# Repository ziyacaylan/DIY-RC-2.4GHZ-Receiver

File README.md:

# DIY-RC-2.4GHZ-Receiver
https://www.thingiverse.com/zii/designs
DIY-RC-2.4GHZ-Receiver

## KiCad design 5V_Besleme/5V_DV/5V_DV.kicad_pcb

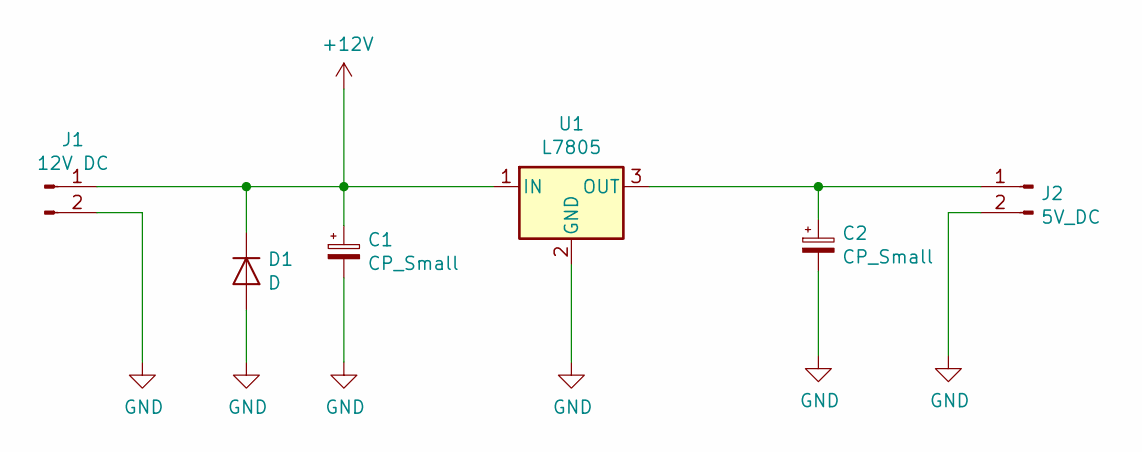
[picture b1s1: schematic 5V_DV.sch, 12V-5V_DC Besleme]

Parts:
C1, C2: CP_Small; CP_Elec_8x6.7
D1: D; D_2114
J1: 12V DC; Socket_Strip_Straight_2x01_Pitch2.54mm
J2: 5V_DC; Socket_Strip_Straight_2x01_Pitch2.54mm
U1: L7805; TO-252-2

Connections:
+12V: C1.1, D1.1 (K), J1.1, U1.1 (IN)
GND: C1.2, C2.2, D1.2 (A), J1.2, J2.2, U1.2 (GND)
unnamed: C2.1, J2.1, U1.3 (OUT)

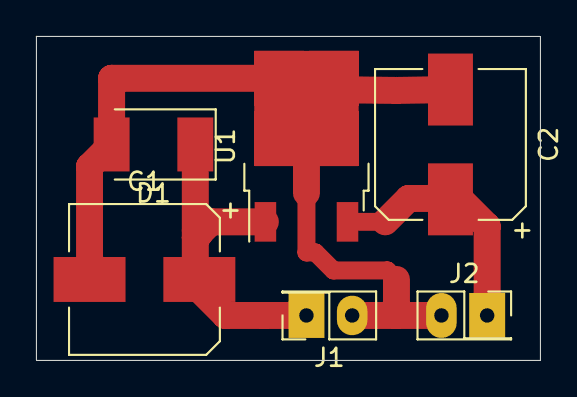
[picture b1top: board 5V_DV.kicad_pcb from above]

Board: 2 copper layers, 28.0 x 18.0 mm, 6 parts (0 on the bottom side), 3 nets.

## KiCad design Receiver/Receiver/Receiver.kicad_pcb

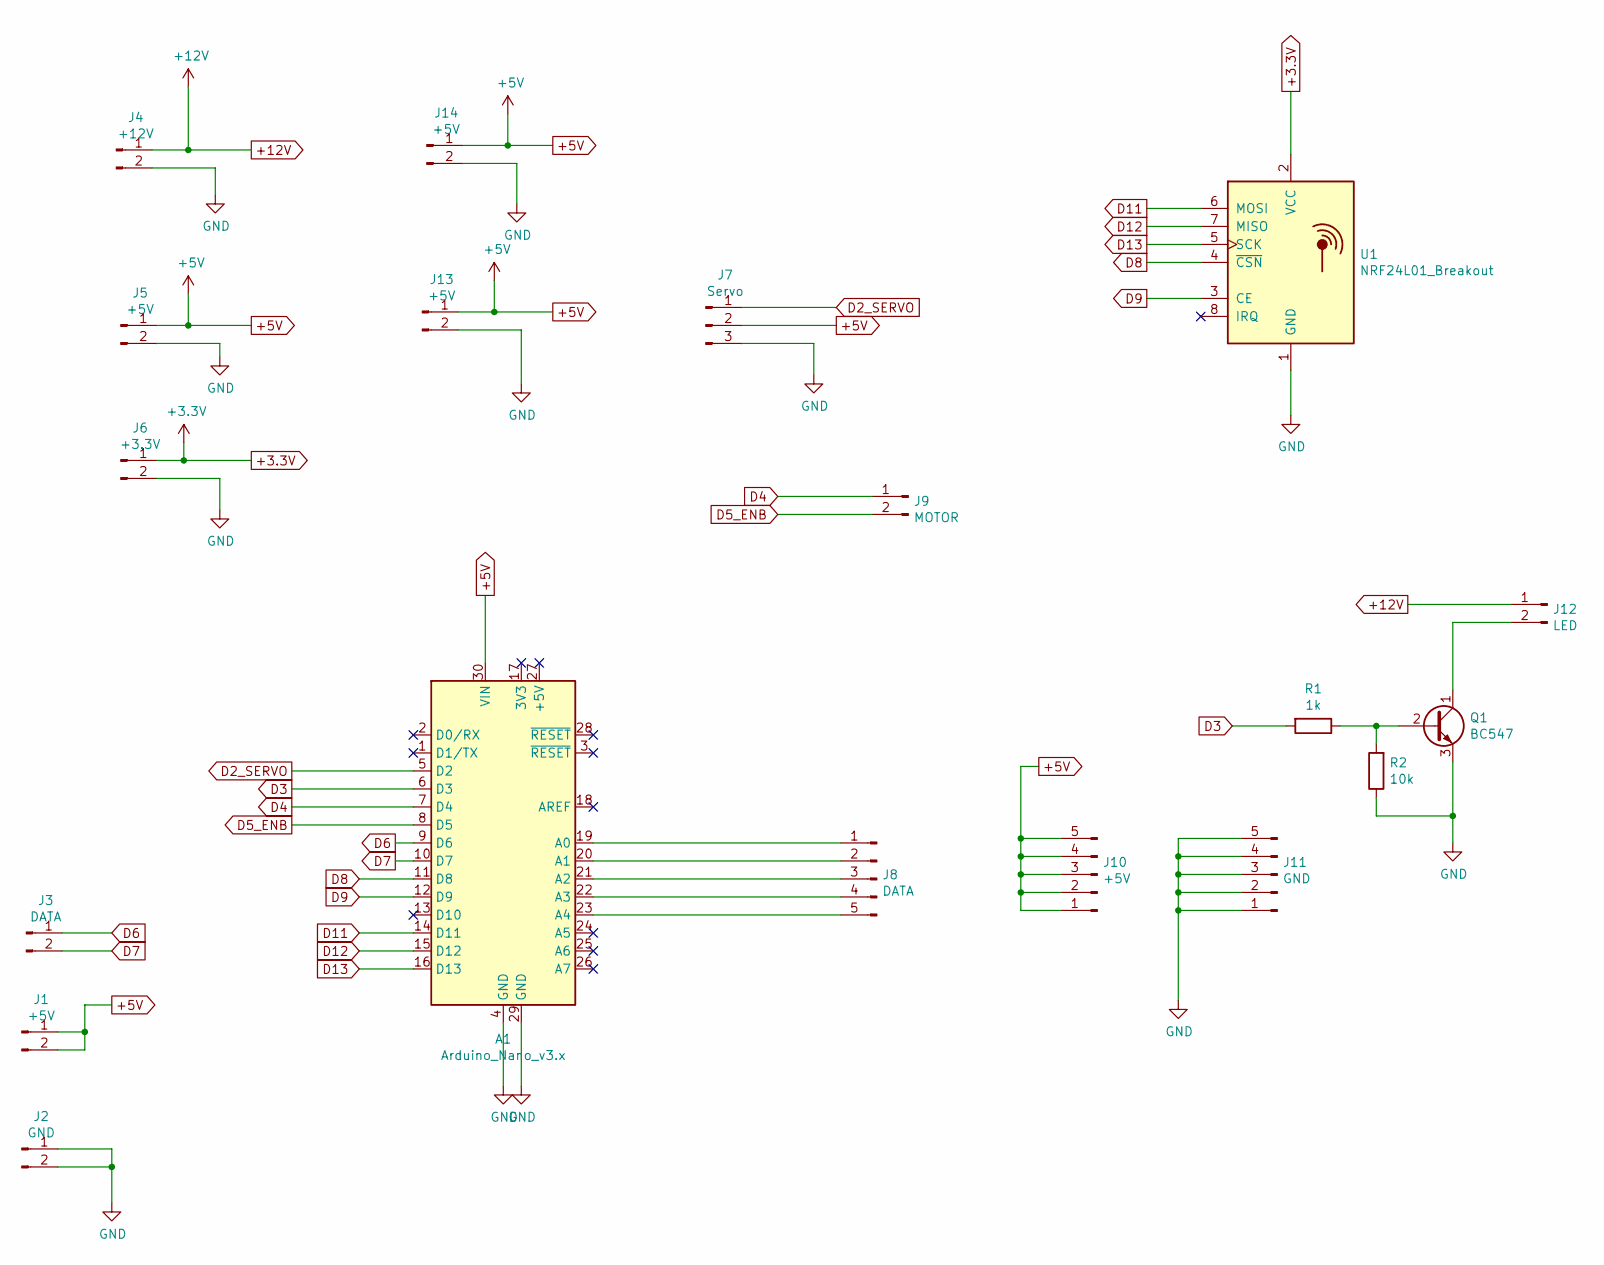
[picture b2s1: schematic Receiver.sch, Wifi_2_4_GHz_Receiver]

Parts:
A1: Arduino_Nano_v3.x; arduino_nano
J1, J5, J13: +5V; Socket_Strip_Straight_2x01_Pitch2.54mm
J2: GND; Socket_Strip_Straight_2x01_Pitch2.54mm
J3: DATA; Socket_Strip_Straight_2x01_Pitch2.54mm
J4: +12V; Socket_Strip_Straight_2x01_Pitch2.54mm
J6: +3.3V; Socket_Strip_Straight_2x01_Pitch2.54mm
J7: Servo; Socket_Strip_Straight_1x03_Pitch2.54mm
J8: DATA; Socket_Strip_Straight_1x05_Pitch2.54mm
J9: MOTOR; Socket_Strip_Straight_2x01_Pitch2.54mm
J10: +5V; Socket_Strip_Straight_1x05_Pitch2.54mm
J11: GND; Socket_Strip_Straight_1x05_Pitch2.54mm
J12: LED; Socket_Strip_Straight_2x01_Pitch2.54mm
J14: +5V; Socket_Strip_Straight_1x02_Pitch2.54mm
Q1: BC547; TO-92_Inline_Wide
R1: 1k; R_Axial_DIN0207_L6.3mm_D2.5mm_P7.62mm_Horizontal
R2: 10k; R_Axial_DIN0207_L6.3mm_D2.5mm_P7.62mm_Horizontal
U1: NRF24L01_Breakout; NRF24L01Module

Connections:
+3.3V: J6.1, U1.2 (VCC)
+5V: A1.30 (VIN), J1.1, J1.2, J5.1, J7.2, J10.1, J10.2, J10.3, J10.4, J10.5, J13.1, J14.1
+12V: J4.1, J12.1
D2_SERVO: A1.5 (D2), J7.1
D3: A1.6 (D3), R1.2
D4: A1.7 (D4), J9.1
D5_ENB: A1.8 (D5), J9.2
D6: A1.9 (D6), J3.1
D7: A1.10 (D7), J3.2
D8: A1.11 (D8), U1.4 (~CSN)
D9: A1.12 (D9), U1.3 (CE)
D11: A1.14 (D11), U1.6 (MOSI)
D12: A1.15 (D12), U1.7 (MISO)
D13: A1.16 (D13), U1.5 (SCK)
GND: A1.4 (GND), A1.29 (GND), J2.1, J2.2, J4.2, J5.2, J6.2, J7.3, J11.1, J11.2, J11.3, J11.4, J11.5, J13.2, J14.2, Q1.3 (E), R2.1, U1.1 (GND)
unnamed: A1.19 (A0), J8.1
unnamed: A1.20 (A1), J8.2
unnamed: A1.21 (A2), J8.3
unnamed: A1.22 (A3), J8.4
unnamed: A1.23 (A4), J8.5
unnamed: J12.2, Q1.1 (C)
unnamed: Q1.2 (B), R1.1, R2.2

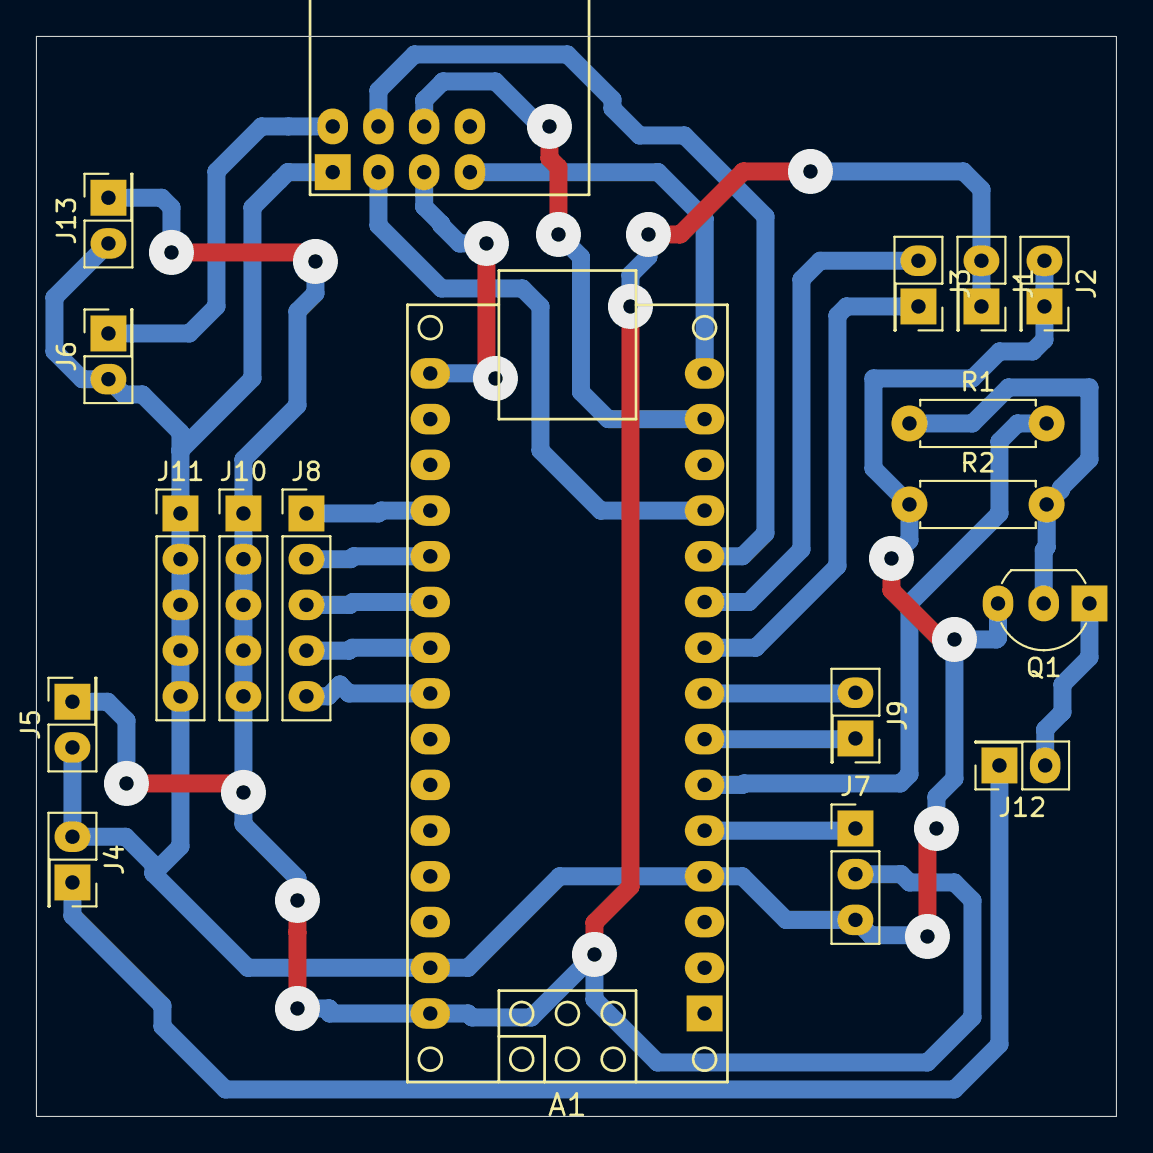
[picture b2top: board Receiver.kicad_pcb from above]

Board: 2 copper layers, 60.0 x 60.0 mm, 18 parts (0 on the bottom side), 22 nets.

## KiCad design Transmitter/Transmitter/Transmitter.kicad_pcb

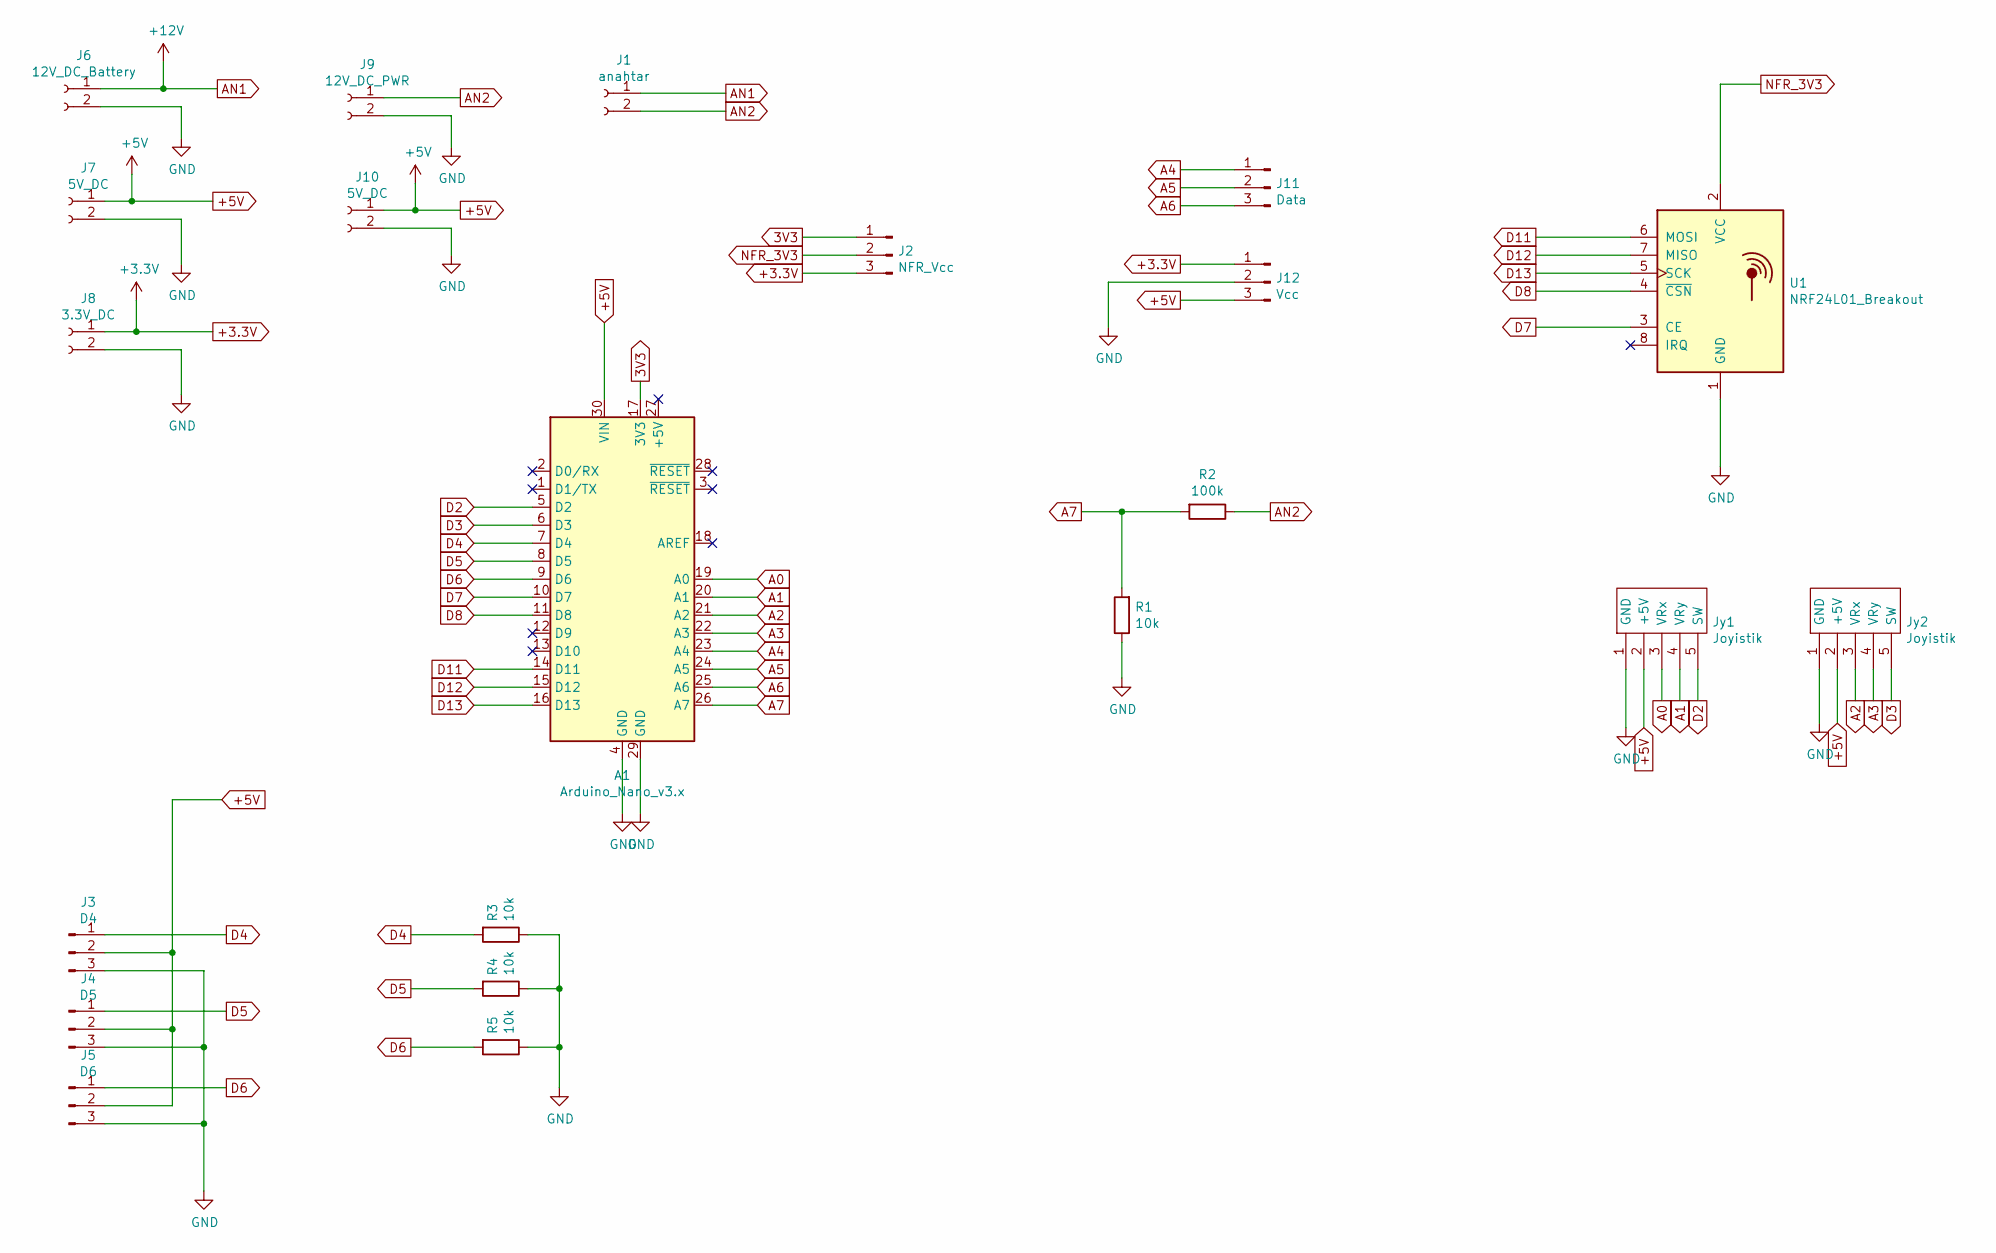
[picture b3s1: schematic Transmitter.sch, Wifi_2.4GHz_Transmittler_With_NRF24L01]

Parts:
A1: Arduino_Nano_v3.x; arduino_nano
J1: anahtar; Socket_Strip_Straight_1x02_Pitch2.54mm
J2: NFR_Vcc; Socket_Strip_Straight_1x03_Pitch2.54mm
J3: D4; Socket_Strip_Straight_1x03_Pitch2.54mm
J4: D5; Socket_Strip_Straight_1x03_Pitch2.54mm
J5: D6; Socket_Strip_Straight_1x03_Pitch2.54mm
J6: 12V_DC_Battery; Socket_Strip_Straight_1x02_Pitch2.54mm
J7, J10: 5V_DC; Socket_Strip_Straight_1x02_Pitch2.54mm
J8: 3.3V_DC; Socket_Strip_Straight_1x02_Pitch2.54mm
J9: 12V_DC_PWR; Socket_Strip_Straight_1x02_Pitch2.54mm
J11: Data; Socket_Strip_Straight_1x03_Pitch2.54mm
J12: Vcc; Socket_Strip_Straight_1x03_Pitch2.54mm
Jy1, Jy2: Joyistik; joyistik
R1, R3, R4, R5: 10k; R_Axial_DIN0207_L6.3mm_D2.5mm_P10.16mm_Horizontal
R2: 100k; R_Axial_DIN0309_L9.0mm_D3.2mm_P15.24mm_Horizontal
U1: NRF24L01_Breakout; NRF24L01Module

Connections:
3V3: A1.17 (3V3), J2.1
+3.3V: J2.3, J8.1, J12.1
+5V: A1.30 (VIN), J3.2, J4.2, J5.2, J7.1, J10.1, J12.3, Jy1.2 (+5V), Jy2.2 (+5V)
A0: A1.19 (A0), Jy1.3 (VRx)
A1: A1.20 (A1), Jy1.4 (VRy)
A2: A1.21 (A2), Jy2.3 (VRx)
A3: A1.22 (A3), Jy2.4 (VRy)
A4: A1.23 (A4), J11.1
A5: A1.24 (A5), J11.2
A6: A1.25 (A6), J11.3
A7: A1.26 (A7), R1.2, R2.2
AN1: J1.1, J6.1
AN2: J1.2, J9.1, R2.1
D2: A1.5 (D2), Jy1.5 (SW)
D3: A1.6 (D3), Jy2.5 (SW)
D4: A1.7 (D4), J3.1, R3.2
D5: A1.8 (D5), J4.1, R4.2
D6: A1.9 (D6), J5.1, R5.2
D7: A1.10 (D7), U1.3 (CE)
D8: A1.11 (D8), U1.4 (~CSN)
D11: A1.14 (D11), U1.6 (MOSI)
D12: A1.15 (D12), U1.7 (MISO)
D13: A1.16 (D13), U1.5 (SCK)
GND: A1.4 (GND), A1.29 (GND), J3.3, J4.3, J5.3, J6.2, J7.2, J8.2, J9.2, J10.2, J12.2, Jy1.1 (GND), Jy2.1 (GND), R1.1, R3.1, R4.1, R5.1, U1.1 (GND)
NFR_3V3: J2.2, U1.2 (VCC)

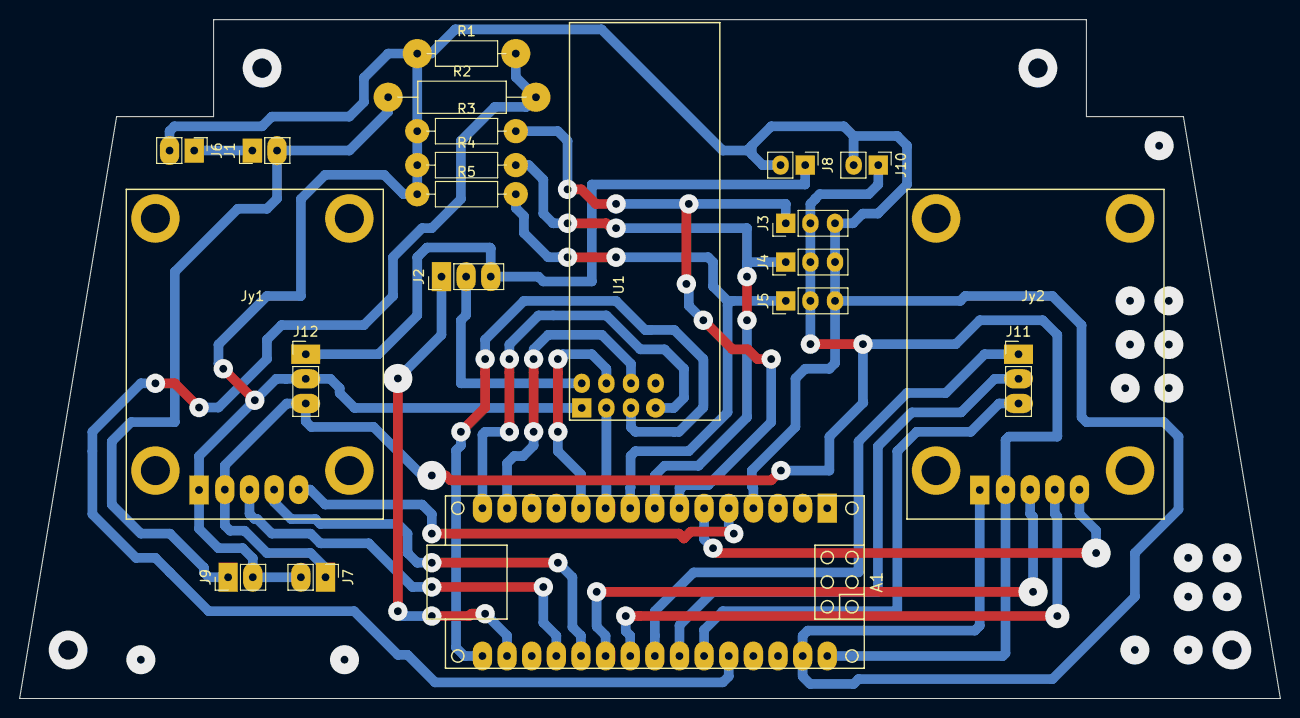
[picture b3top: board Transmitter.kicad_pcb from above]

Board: 2 copper layers, 130.0 x 70.0 mm, 21 parts (0 on the bottom side), 25 nets.

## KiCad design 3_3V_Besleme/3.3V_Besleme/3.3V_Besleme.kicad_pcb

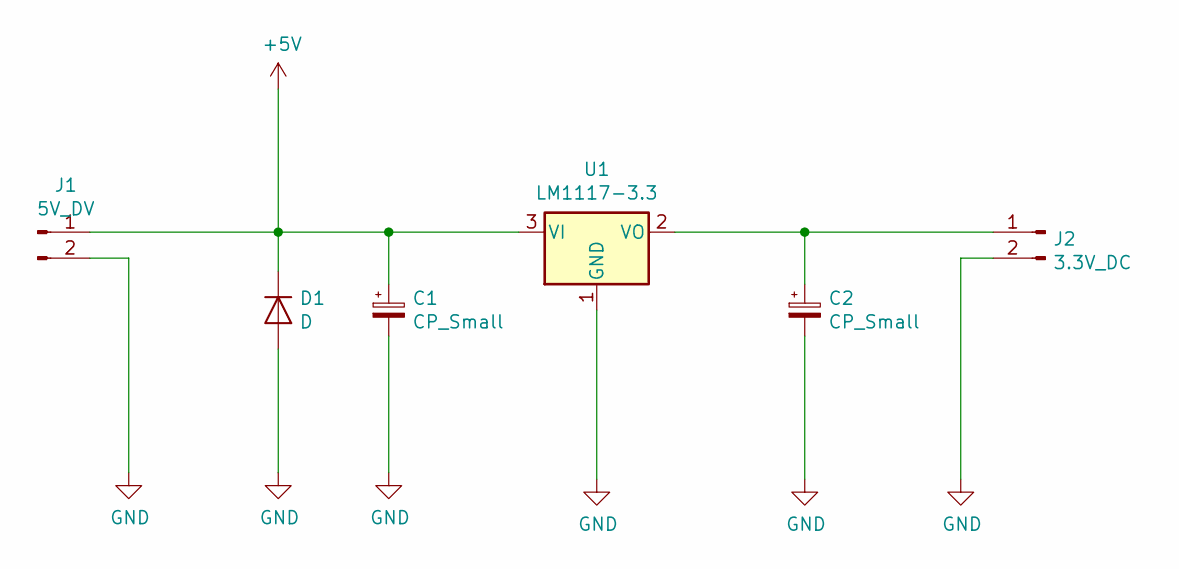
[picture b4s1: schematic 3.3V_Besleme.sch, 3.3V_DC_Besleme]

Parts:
C1, C2: CP_Small; CP_Elec_8x6.5
D1: D; D_2114
J1: 5V_DV; Socket_Strip_Straight_1x02_Pitch2.54mm
J2: 3.3V_DC; Socket_Strip_Straight_1x02_Pitch2.54mm
U1: LM1117-3.3; TO-252-2

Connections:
+5V: C1.1, D1.1 (K), J1.1, U1.3 (VI)
GND: C1.2, C2.2, D1.2 (A), J1.2, J2.2, U1.1 (GND)
unnamed: C2.1, J2.1, U1.2 (VO)

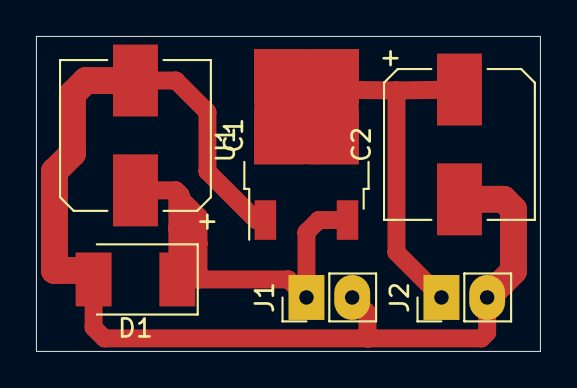
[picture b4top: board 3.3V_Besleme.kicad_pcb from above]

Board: 2 copper layers, 28.0 x 17.5 mm, 6 parts (0 on the bottom side), 3 nets.

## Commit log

2022-02-09 DIY-RC-2.4GHZ-Receiver
